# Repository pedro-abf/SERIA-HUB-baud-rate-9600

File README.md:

# SERIA-HUB
The purpose of this hardware is to facilitate the development of systems with many serial connections.
At this moment, the hardware is functional but the design has to be reviewed to increase its capabilities and simplify the assembly and bill of materials.

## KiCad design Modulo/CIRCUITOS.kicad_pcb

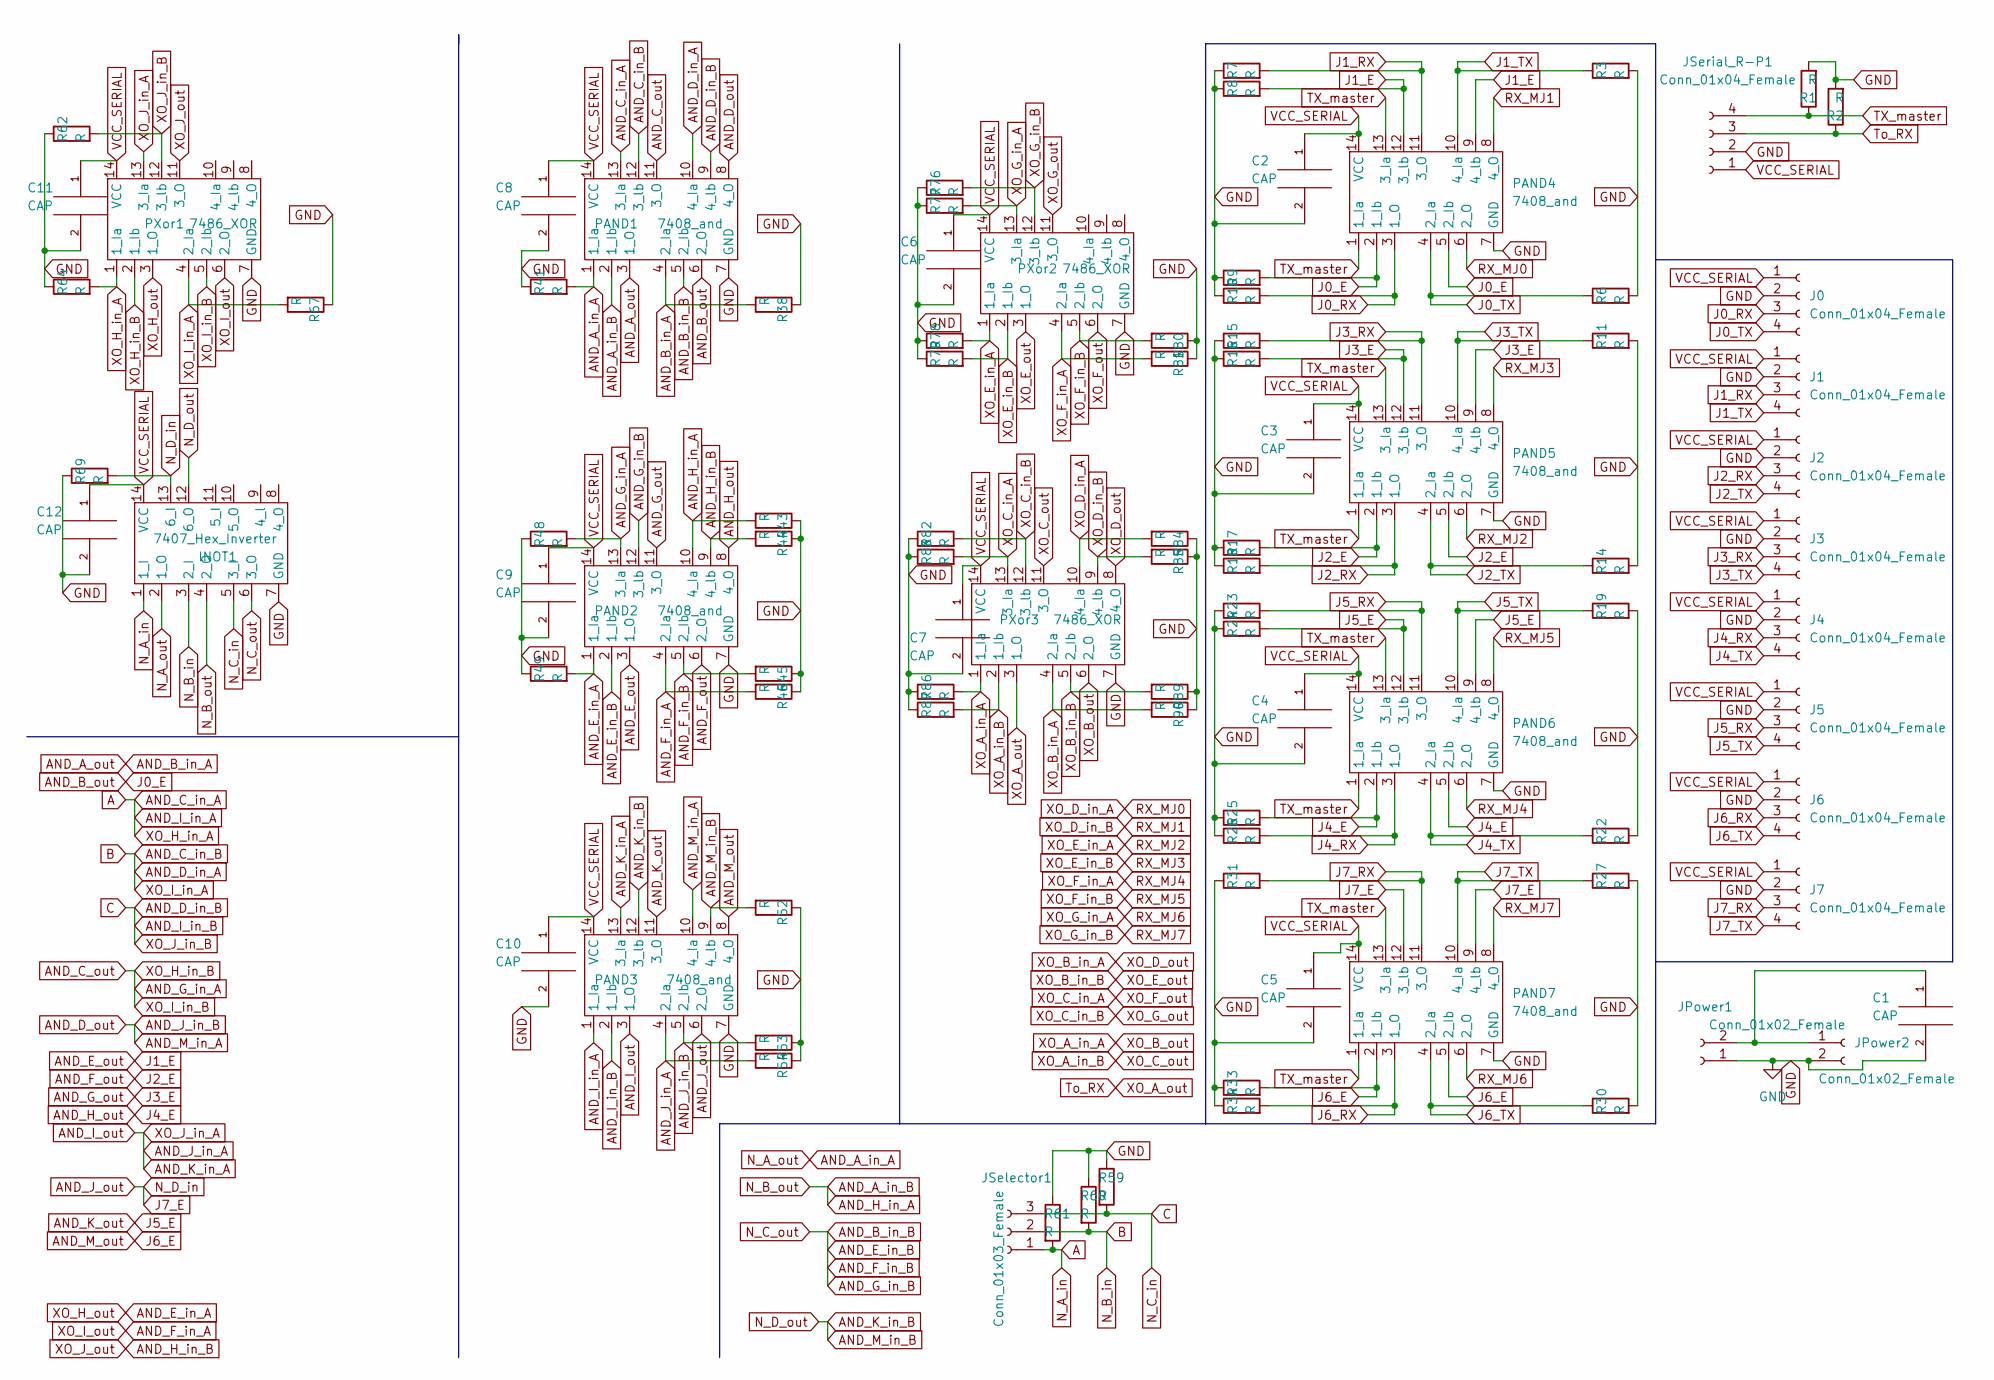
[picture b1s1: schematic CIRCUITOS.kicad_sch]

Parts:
C1, C2, C3, C4, C5, C6, C7, C8, C9, C10, C11, C12: CAP; C_Rect_L4.0mm_W2.5mm_P2.50mm
INOT1: 7407_Hex_Inverter; DIP-14_W7.62mm
J0, J1, J2, J3, J4, J5, J6, J7: Conn_01x04_Female; Conn 4x5
JPower1, JPower2: Conn_01x02_Female; Conn2x5
JSelector1: Conn_01x03_Female; Conn 35
JSerial_R-P1: Conn_01x04_Female; Conn 4x5
PAND1, PAND2, PAND3, PAND4, PAND5, PAND6, PAND7: 7408_and; DIP-14_W7.62mm
PXor1, PXor2, PXor3: 7486_XOR; DIP-14_W7.62mm
R1, R2, R3, R6, R7, R8, R9, R10, R11, R14, R15, R16, R17, R18, R19, R22, R23, R24, R25, R26, R27, R30, R31, R33, R34, R38, R41, R43, R44, R45, R46, R48, R49, R52, R53, R54, R59, R60, R61, R62, R64, R67, R69, R76, R77, R78, R79, R80, R81, R82, R83, R84, R85, R86, R87, R89, R90: R; R_Axial_DIN0207_L6.3mm_D2.5mm_P10.16mm_Horizontal

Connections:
A: INOT1.1 (1_I), JSelector1.1, PAND1.13 (3_Ia), PAND3.1 (1_Ia), PXor1.1 (1_Ia), R61.2, R64.2
AND_A_in_A: INOT1.2 (1_O), PAND1.1 (1_Ia), R41.2
AND_A_in_B: INOT1.4 (2_O), PAND1.2 (1_Ib), PAND2.10 (4_Ia), R43.2
AND_A_out: PAND1.3 (1_O), PAND1.4 (2_Ia), R38.2
AND_B_in_B: INOT1.6 (3_O), PAND1.5 (2_Ib), PAND2.2 (1_Ib), PAND2.5 (2_Ib), PAND2.12 (3_lb), R45.2
AND_B_out: PAND1.6 (2_O), PAND4.2 (1_Ib), PAND4.5 (2_Ib), R9.2
AND_C_in_B: INOT1.3 (2_I), JSelector1.2, PAND1.10 (4_Ia), PAND1.12 (3_lb), PXor1.4 (2_Ia), R60.2, R67.2
AND_C_out: PAND1.11 (3_O), PAND2.13 (3_Ia), PXor1.2 (1_Ib), PXor1.5 (2_Ib), R48.2
AND_D_in_B: INOT1.5 (3_I), JSelector1.3, PAND1.9 (4_lb), PAND3.2 (1_Ib), PXor1.12 (3_lb), R59.2, R62.2; also elsewhere on the board
AND_D_out: PAND1.8 (4_O), PAND3.5 (2_Ib), PAND3.10 (4_Ia), R53.2
AND_E_in_A: PAND2.1 (1_Ia), PXor1.3 (1_O), R49.2
AND_E_out: PAND2.3 (1_O), PAND4.9 (4_lb), PAND4.12 (3_lb), R8.2
AND_F_in_A: PAND2.4 (2_Ia), PXor1.6 (2_O), R46.2
AND_F_out: PAND2.6 (2_O), PAND5.2 (1_Ib), PAND5.5 (2_Ib), R17.2
AND_G_out: PAND2.11 (3_O), PAND5.9 (4_lb), PAND5.12 (3_lb), R16.2
AND_H_in_B: PAND2.9 (4_lb), PXor1.11 (3_O), R44.2
AND_H_out: PAND2.8 (4_O), PAND6.2 (1_Ib), PAND6.5 (2_Ib), R25.2
AND_I_out: PAND3.3 (1_O), PAND3.4 (2_Ia), PAND3.13 (3_Ia), PXor1.13 (3_Ia), R54.2
AND_J_out: INOT1.13 (6_I), PAND3.6 (2_O), PAND7.9 (4_lb), PAND7.12 (3_lb), R69.2
AND_K_in_B: INOT1.12 (6_O), PAND3.9 (4_lb), PAND3.12 (3_lb), R52.2
AND_K_out: PAND3.11 (3_O), PAND6.9 (4_lb), PAND6.12 (3_lb), R24.2
AND_M_out: PAND3.8 (4_O), PAND7.2 (1_Ib), PAND7.5 (2_Ib), R33.2
GND: C1.2, C2.2, C3.2, C4.2, C5.2, C6.2, C7.2, C8.2, C9.2, C10.2, C11.2, C12.2, INOT1.7 (GND), J0.2, J1.2, J2.2, J3.2, J4.2, J5.2, J6.2, J7.2, JPower1.1, JPower2.2, JSerial_R-P1.2, PAND1.7 (GND), PAND2.7 (GND), PAND3.7 (GND), PAND4.7 (GND), PAND5.7 (GND), PAND6.7 (GND), PAND7.7 (GND), PXor1.7 (GND), PXor2.7 (GND), PXor3.7 (GND), R1.2, R2.2, R3.2, R6.2, R7.1, R8.1, R9.1, R10.1, R11.2, R14.2, R15.1, R16.1, R17.1, R18.1, R19.2, R22.2, R23.1, R24.1, R25.1, R26.1, R27.2, R30.2, R31.1, R33.1, R34.1, R38.1, R41.1, R43.1, R44.1, R45.1, R46.1, R48.1, R49.1, R52.1, R53.1, R54.1, R59.1, R60.1, R61.1, R62.1, R64.1, R67.1, R69.1, R76.1, R77.1, R78.1, R79.1, R80.1, R81.1, R82.1, R83.1, R84.1, R85.1, R86.1, R87.1, R89.1, R90.1; also elsewhere on the board
J0_RX: J0.3, PAND4.3 (1_O), R10.2
J0_TX: J0.4, PAND4.4 (2_Ia), R6.1
J1_RX: J1.3, PAND4.11 (3_O), R7.2
J1_TX: J1.4, PAND4.10 (4_Ia), R3.1
J2_RX: J2.3, PAND5.3 (1_O), R18.2
J2_TX: J2.4, PAND5.4 (2_Ia), R14.1
J3_RX: J3.3, PAND5.11 (3_O), R15.2
J3_TX: J3.4, PAND5.10 (4_Ia), R11.1
J4_RX: J4.3, PAND6.3 (1_O), R26.2
J4_TX: J4.4, PAND6.4 (2_Ia), R22.1
J5_RX: J5.3, PAND6.11 (3_O), R23.2
J5_TX: J5.4, PAND6.10 (4_Ia), R19.1
J6_RX: J6.3, PAND7.3 (1_O), R34.2
J6_TX: J6.4, PAND7.4 (2_Ia), R30.1
J7_RX: J7.3, PAND7.11 (3_O), R31.2
J7_TX: J7.4, PAND7.10 (4_Ia), R27.1
unnamed: C1.1, JPower1.2, JPower2.1
RX_MJ0: PAND4.6 (2_O), PXor3.10 (4_Ia), R84.2
RX_MJ1: PAND4.8 (4_O), PXor3.9 (4_lb), R85.2
RX_MJ2: PAND5.6 (2_O), PXor2.1 (1_Ia), R78.2
RX_MJ3: PAND5.8 (4_O), PXor2.2 (1_Ib), R79.2
RX_MJ4: PAND6.6 (2_O), PXor2.4 (2_Ia), R81.2
RX_MJ5: PAND6.8 (4_O), PXor2.5 (2_Ib), R80.2
RX_MJ6: PAND7.6 (2_O), PXor2.13 (3_Ia), R77.2
RX_MJ7: PAND7.8 (4_O), PXor2.12 (3_lb), R76.2
TX_master: JSerial_R-P1.4, PAND4.1 (1_Ia), PAND4.13 (3_Ia), PAND5.1 (1_Ia), PAND5.13 (3_Ia), PAND6.1 (1_Ia), PAND6.13 (3_Ia), PAND7.1 (1_Ia), PAND7.13 (3_Ia), R1.1
To_RX: JSerial_R-P1.3, PXor3.3 (1_O), R2.1
VCC_SERIAL: C2.1, C3.1, C4.1, C5.1, C6.1, C7.1, C8.1, C9.1, C10.1, C11.1, C12.1, INOT1.14 (VCC), J0.1, J1.1, J2.1, J3.1, J4.1, J5.1, J6.1, J7.1, JSerial_R-P1.1, PAND1.14 (VCC), PAND2.14 (VCC), PAND3.14 (VCC), PAND4.14 (VCC), PAND5.14 (VCC), PAND6.14 (VCC), PAND7.14 (VCC), PXor1.14 (VCC), PXor2.14 (VCC), PXor3.14 (VCC)
XO_A_in_A: PXor3.1 (1_Ia), PXor3.6 (2_O), R86.2
XO_A_in_B: PXor3.2 (1_Ib), PXor3.11 (3_O), R87.2
XO_B_in_A: PXor3.4 (2_Ia), PXor3.8 (4_O), R90.2
XO_B_in_B: PXor2.3 (1_O), PXor3.5 (2_Ib), R89.2
XO_C_in_A: PXor2.6 (2_O), PXor3.13 (3_Ia), R83.2
XO_C_in_B: PXor2.11 (3_O), PXor3.12 (3_lb), R82.2

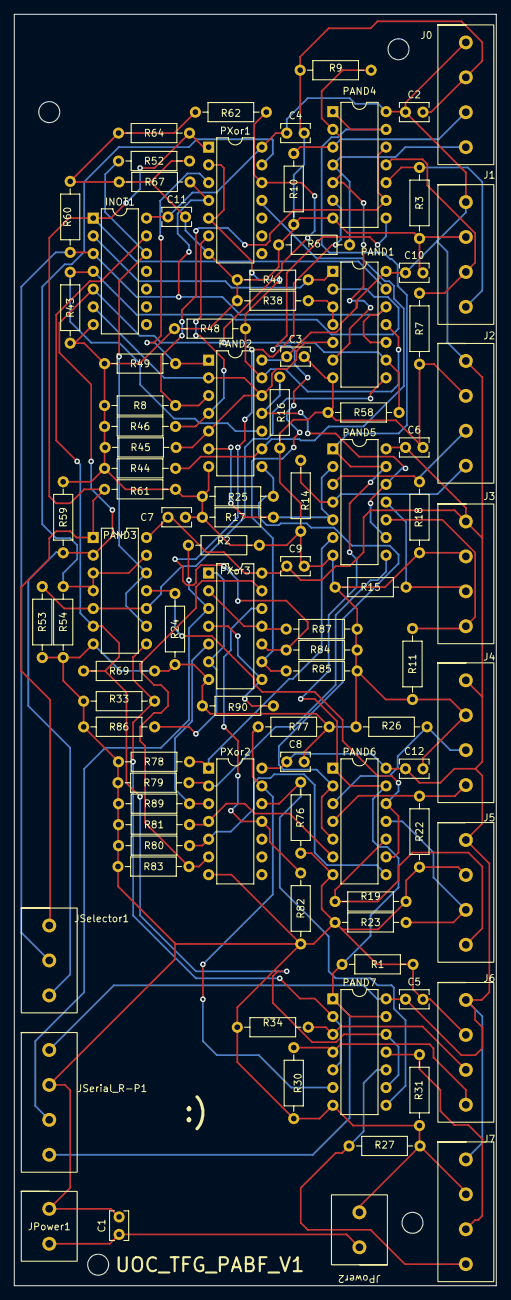
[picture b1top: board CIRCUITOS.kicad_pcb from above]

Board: 2 copper layers, 69.0 x 182.0 mm, 93 parts (0 on the bottom side), 57 nets.

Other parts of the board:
R58: R; R_Axial_DIN0207_L6.3mm_D2.5mm_P10.16mm_Horizontal

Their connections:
AND_D_in_B: R58.2; also elsewhere on the board
GND: R58.1; also elsewhere on the board

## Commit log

2023-05-27 Create component
2023-05-27 Rename component to components
